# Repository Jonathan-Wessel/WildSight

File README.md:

# WildSights Rhino Detection Camera Node

This project is an ESP32-S3 wildlife monitoring camera node that detects rhinos using an Edge Impulse object detection model. The device is triggered by a PIR motion sensor, captures a grayscale image, runs inference on-device, saves the captured image to an SD card, and sends a LoRaWAN uplink message with the detection result.

The project is currently configured for the `ESP32S3-EYE` camera model.

---

## Features

- PIR motion-triggered image capture
- ESP32-S3 camera support
- Edge Impulse object detection
- Rhino detection using bounding box results
- Grayscale QVGA camera capture
- SD card image saving as JPEG
- LoRaWAN uplinks using LMIC
- IR LED control for low-light image capture
- FreeRTOS task for image capture and inference

---

## Important Board Manager Version

Use the following ESP32 board package version:

```text
ESP32 by Espressif Systems version 2.0.17
```

In the Arduino IDE:

1. Open **Tools > Board > Boards Manager**
2. Search for **esp32**
3. Install **esp32 by Espressif Systems**
4. Select version **2.0.17**

Using a newer or different ESP32 board package version may cause compatibility issues with the camera, PSRAM, SD card, or libraries.

---

## Hardware Requirements

- ESP32-S3 camera board
- ESP32S3-EYE compatible camera pin configuration
- PIR motion sensor
- IR LED or IR illuminator
- Light sensor
- SD card
- LoRa radio module
- LoRaWAN gateway
- LoRaWAN network server, such as The Things Network

---

## Software Requirements

- Arduino IDE
- ESP32 Arduino board package version `2.0.17`
- MCCI LoRaWAN LMIC library
- Edge Impulse Arduino library exported from the Edge Impulse project
- ESP32 camera support
- SD_MMC support

The sketch also requires these project files:

```cpp
#include "camera_pins.h"
#include "sd_read_write.h"
```

Make sure these files are included in the sketch folder or are available through the correct library or example source.

---

## Recommended Arduino IDE Settings

| Setting | Value |
|---|---|
| Board package | ESP32 by Espressif Systems `2.0.17` |
| Board | ESP32S3 Dev Module or compatible ESP32-S3 camera board |
| PSRAM | Enabled |
| Upload speed | 921600 or lower if upload fails |
| Serial monitor baud | 115200 |
| Partition scheme | Huge APP or another large-app partition |

The exact board option may depend on the ESP32-S3 camera board being used.

---

## Pin Configuration

### Sensor and Output Pins

| Function | GPIO |
|---|---:|
| PIR sensor | GPIO 1 |
| IR LED | GPIO 2 |
| Light sensor | GPIO 46 |

### LoRa Radio Pins

| Function | GPIO |
|---|---:|
| NSS / CS | GPIO 3 |
| RESET | GPIO 14 |
| DIO0 | GPIO 20 |
| DIO1 | GPIO 21 |
| MISO | GPIO 47 |
| MOSI | GPIO 19 |
| SCK | GPIO 45 |

These pins are defined in the sketch:

```cpp
#define GPIO_PIR         1
#define GPIO_IRLED       2
#define GPIO_LIGHTSENSOR 46

#define PIN_NSS   3
#define PIN_RST   14
#define PIN_DIO0  20
#define PIN_DIO1  21

#define LORA_MISO  47
#define LORA_MOSI  19
#define LORA_SCK   45
```

Check that the pin definitions match the actual wiring of your ESP32-S3 board and LoRa module.

---

## Camera Configuration

The project is configured for:

```cpp
#define CAMERA_MODEL_ESP32S3_EYE
```

The camera captures grayscale QVGA images:

```cpp
.pixel_format = PIXFORMAT_GRAYSCALE,
.frame_size   = FRAMESIZE_QVGA,
```

This means the camera captures images at:

```text
320 x 240
```

The frame buffer is stored in PSRAM:

```cpp
.fb_location = CAMERA_FB_IN_PSRAM
```

Because of this, PSRAM must be enabled in the Arduino IDE board settings.

---

## Edge Impulse Model

The project uses an exported Edge Impulse model:

```cpp
#include <Wildsights_rhino_md_conf.5_inferencing.h>
```

The classifier is initialized in `setup()`:

```cpp
run_classifier_init();
```

Inference is run using:

```cpp
EI_IMPULSE_ERROR err = run_classifier(&signal, &result, false);
```

The code checks the Edge Impulse bounding box results for the label:

```text
rhino
```

The label comparison happens here:

```cpp
if (strcmp(bb.label, "rhino") == 0)
```

If your Edge Impulse model uses a different label name, update this line in the sketch.

---

## Detection Threshold

The rhino detection confidence threshold is currently set to `0.7`:

```cpp
if (rhino && best.value >= 0.7) {
```

Threshold behavior:

| Threshold | Behavior |
|---|---|
| `0.5` | More sensitive, but may create more false positives |
| `0.7` | Current default |
| `0.9` | More strict, but may miss some detections |

---

## LoRaWAN Configuration

The sketch uses OTAA activation with:

- Join EUI
- Device EUI
- App Key

These values are defined in the code:

```cpp
static const uint8_t JOIN_EUI_BE[8] = { ... };
static const uint8_t DEV_EUI_BE[8]  = { ... };
static const uint8_t APP_KEY[16]    = { ... };
```

Do not publish real LoRaWAN credentials in a public repository.

For public repositories, replace real credentials with placeholder values:

```cpp
static const uint8_t JOIN_EUI_BE[8] = {
  0x00, 0x00, 0x00, 0x00,
  0x00, 0x00, 0x00, 0x00
};

static const uint8_t DEV_EUI_BE[8] = {
  0x00, 0x00, 0x00, 0x00,
  0x00, 0x00, 0x00, 0x00
};

static const uint8_t APP_KEY[16] = {
  0x00, 0x00, 0x00, 0x00,
  0x00, 0x00, 0x00, 0x00,
  0x00, 0x00, 0x00, 0x00,
  0x00, 0x00, 0x00, 0x00
};
```

If real keys were shared publicly, regenerate them in your LoRaWAN network server.

---

## LMIC Configuration

The LoRa radio uses custom SPI pins:

```cpp
SPI.begin(LORA_SCK, LORA_MISO, LORA_MOSI, PIN_NSS);
```

LMIC is initialized in `setup()`:

```cpp
os_init();
LMIC_reset();
LMIC_selectSubBand(1);
LMIC_setAdrMode(0);
LMIC_setClockError(MAX_CLOCK_ERROR * 1 / 100);
LMIC_startJoining();
```

The selected LoRaWAN sub-band is:

```cpp
LMIC_selectSubBand(1);
```

Make sure this matches your LoRaWAN region, gateway, and network server configuration.

---

## LoRaWAN Uplink Messages

When a rhino is detected, the node sends:

```text
Rhino detected
```

When no rhino is detected, the node sends:

```text
No Rhino
```

Messages are sent on LoRaWAN port `1`:

```cpp
LMIC_setTxData2(1, buf, (u1_t)len, 0);
```

---

## SD Card Image Saving

Images are saved to:

```text
/camera/
```

The directory is created during setup:

```cpp
createDir(SD_MMC, "/camera");
```

Images are saved using an incrementing file number:

```text
/camera/1.jpg
/camera/2.jpg
/camera/3.jpg
```

Both rhino detections and non-detections are currently saved.

---

## How It Works

1. The ESP32-S3 starts the serial monitor, SD card, camera, Edge Impulse model, LoRa radio, and PIR interrupt.
2. The PIR sensor triggers an interrupt when motion is detected.
3. A FreeRTOS inference task wakes up.
4. The PIR signal is debounced.
5. The IR LED turns on.
6. The camera captures a grayscale image.
7. The image is resized to the Edge Impulse model input size.
8. The Edge Impulse classifier runs on the ESP32-S3.
9. The result is checked for a bounding box labeled `rhino`.
10. If the confidence is at least `0.7`, a rhino detection is confirmed.
11. The image is saved to the SD card.
12. A LoRaWAN message is queued.
13. The IR LED turns off.
14. The system waits through a cooldown period before responding to another trigger.

---

## Main Runtime Loop

The main `loop()` only runs the LMIC event loop:

```cpp
void loop() {
  os_runloop_once();
}
```

Image capture and inference are handled in a separate FreeRTOS task:

```cpp
xTaskCreatePinnedToCore(
  inferenceTask,
  "inferenceTask",
  32768,
  nullptr,
  1,
  &inferTaskHandle,
  1
);
```

---

## Serial Monitor

Open the Serial Monitor at:

```text
115200 baud
```

Startup messages include:

```text
PSRAM found: YES
Free heap:
Free PSRAM:
Camera PID:
Setup complete.
```

LoRaWAN messages include:

```text
Joining...
JOINED!
Uplink queued: Rhino detected
TX complete
```

Inference messages include:

```text
INFERENCE: running classifier
INFERENCE: done classifier
Rhino DETECTED
No rhino.
```

---

## Troubleshooting

### Camera Init Failed

Check the following:

- The correct camera model is selected
- `camera_pins.h` matches your board
- PSRAM is enabled
- ESP32 board package version is `2.0.17`
- The camera ribbon cable is connected correctly

### Failed to Allocate Snapshot Buffer

Check the following:

- PSRAM is enabled
- The board has PSRAM
- The Edge Impulse model is not too large
- The partition scheme provides enough app space

### Device Does Not Join LoRaWAN

Check the following:

- Join EUI
- Device EUI
- App Key
- EUI byte order
- LMIC region
- LMIC sub-band
- Gateway frequency plan
- LoRa radio wiring
- Antenna connection

### SD Card Images Are Not Saving

Check the following:

- SD card is inserted
- SD card is formatted correctly
- `sdmmcInit()` succeeds
- The `/camera` directory exists
- `sd_read_write.h` is included correctly

### Classifier Always Returns No Rhino

Check the following:

- The model label is exactly `rhino`
- The detection threshold is not too high
- The camera image orientation is correct
- The IR LED provides enough illumination
- The training data matches the deployment environment
- The model was exported correctly from Edge Impulse

---

## Notes

The function:

```cpp
saveGrayJpegWithBox()
```

saves the grayscale camera frame as a JPEG image.

In the current version of the sketch, the bounding box is printed to the Serial Monitor but is not drawn onto the saved image.

The bounding box output is printed here:

```cpp
Serial.printf(
  "Rhino DETECTED label = %s : conf=%.3f box(x=%u y=%u w=%u h=%u)\n",
  best.label,
  best.value,
  best.x,
  best.y,
  best.width,
  best.height
);
```

---

## Deployment Notes

- Use a weatherproof enclosure for outdoor deployment.
- Protect the camera lens, PIR sensor, and electronics from rain.
- Use a stable power supply.
- Connect the LoRa antenna before transmitting.
- Test the camera, SD card, Edge Impulse model, and LoRaWAN join process before field deployment.
- Do not publish real LoRaWAN credentials.

---

## License

Add the project license here.

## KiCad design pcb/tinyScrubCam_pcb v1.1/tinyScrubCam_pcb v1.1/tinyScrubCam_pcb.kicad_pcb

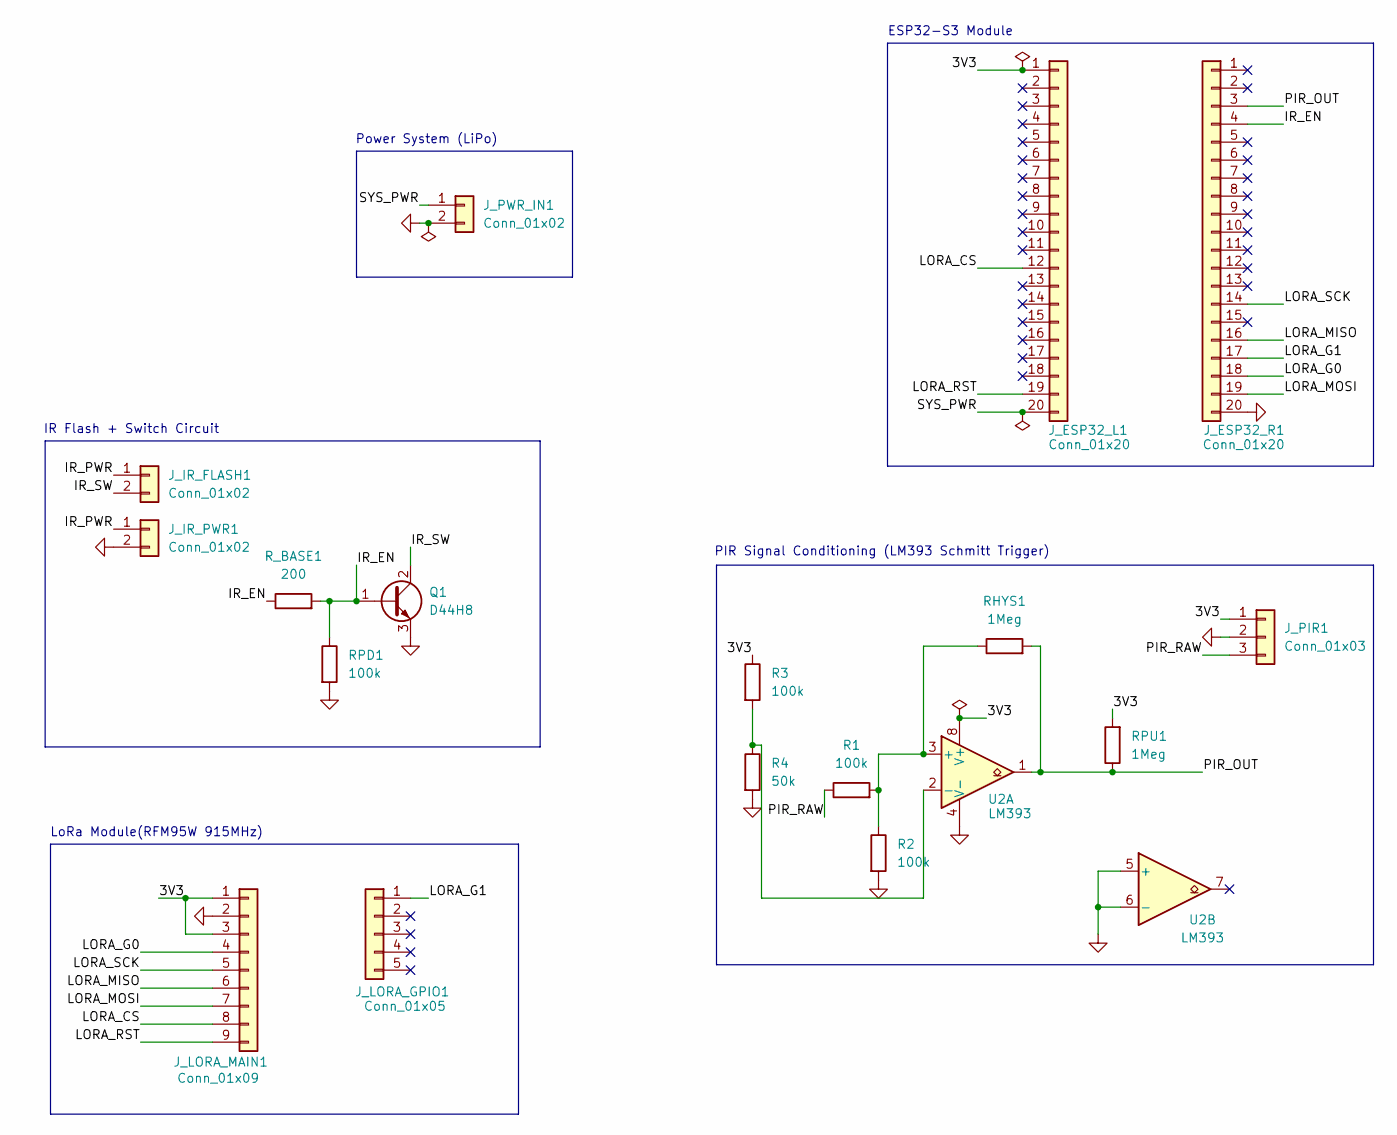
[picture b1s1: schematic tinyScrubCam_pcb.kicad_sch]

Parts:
J_ESP32_L1, J_ESP32_R1: Conn_01x20; PinHeader_1x20_P2.54mm_Vertical
J_IR_FLASH1: Conn_01x02; PinHeader_1x02_P2.54mm_Vertical
J_IR_PWR1: Conn_01x02; PinHeader_1x02_P2.54mm_Vertical
J_LORA_GPIO1: Conn_01x05; PinHeader_1x05_P2.54mm_Vertical
J_LORA_MAIN1: Conn_01x09; PinHeader_1x09_P2.54mm_Vertical
J_PIR1: Conn_01x03; PinSocket_1x03_P2.54mm_Vertical
J_PWR_IN1: Conn_01x02; JST_PH_B2B-PH-K_1x02_P2.00mm_Vertical
Q1: D44H8; TO-220-3_Vertical
R1, R2, R3: 100k; R_Axial_DIN0207_L6.3mm_D2.5mm_P10.16mm_Horizontal
R4: 50k; R_Axial_DIN0207_L6.3mm_D2.5mm_P10.16mm_Horizontal
RHYS1: 1Meg; R_Axial_DIN0207_L6.3mm_D2.5mm_P10.16mm_Horizontal
RPD1: 100k; R_Axial_DIN0207_L6.3mm_D2.5mm_P10.16mm_Horizontal
RPU1: 1Meg; R_Axial_DIN0207_L6.3mm_D2.5mm_P10.16mm_Horizontal
R_BASE1: 200; R_Axial_DIN0207_L6.3mm_D2.5mm_P10.16mm_Horizontal
U2: LM393

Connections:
/3V3: J_ESP32_L1.1 (3V3), J_LORA_MAIN1.1 (3V3), J_LORA_MAIN1.3 (EN), J_PIR1.1, R3.1, RPU1.2, U2.8 (V+); also elsewhere on the board
/IR_EN: J_ESP32_R1.4 (GPIO2), Q1.1 (B), RPD1.1, R_BASE1.1, R_BASE1.2
/IR_PWR: J_IR_FLASH1.1, J_IR_PWR1.1
/IR_SW: J_IR_FLASH1.2, Q1.2 (C)
/LORA_CS: J_ESP32_L1.12 (GPIO3), J_LORA_MAIN1.8 (CS)
/LORA_G0: J_ESP32_R1.18 (GPIO20), J_LORA_MAIN1.4 (GPIO0)
/LORA_G1: J_ESP32_R1.17 (GPIO21), J_LORA_GPIO1.1 (GPIO1_1)
/LORA_MISO: J_ESP32_R1.16 (GPIO47), J_LORA_MAIN1.6 (MISO)
/LORA_MOSI: J_ESP32_R1.19 (GPIO19), J_LORA_MAIN1.7 (MOSI)
/LORA_RST: J_ESP32_L1.19 (GPIO14), J_LORA_MAIN1.9 (RST)
/LORA_SCK: J_ESP32_R1.14 (GPIO45), J_LORA_MAIN1.5 (SCK)
/PIR_OUT: J_ESP32_R1.3 (GPIO1), RHYS1.2, RPU1.1, U2.1
/PIR_RAW: J_PIR1.3, R1.1; also elsewhere on the board
/SYS_PWR: J_ESP32_L1.20 (5V), J_PWR_IN1.1
GND: J_ESP32_R1.20 (GND), J_IR_PWR1.2, J_LORA_MAIN1.2 (GND), J_PIR1.2, J_PWR_IN1.2, Q1.3 (E), R2.2, R4.2, RPD1.2, U2.4 (V-), U2.5 (+), U2.6 (-); also elsewhere on the board
unnamed: R1.2, R2.1, RHYS1.1, U2.3 (+)
unnamed: R3.2, R4.1, U2.2 (-)

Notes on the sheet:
ESP32-S3 Module
IR Flash + Switch Circuit
Power System (LiPo)
LoRa Module(RFM95W 915MHz)
PIR Signal Conditioning (LM393 Schmitt Trigger)

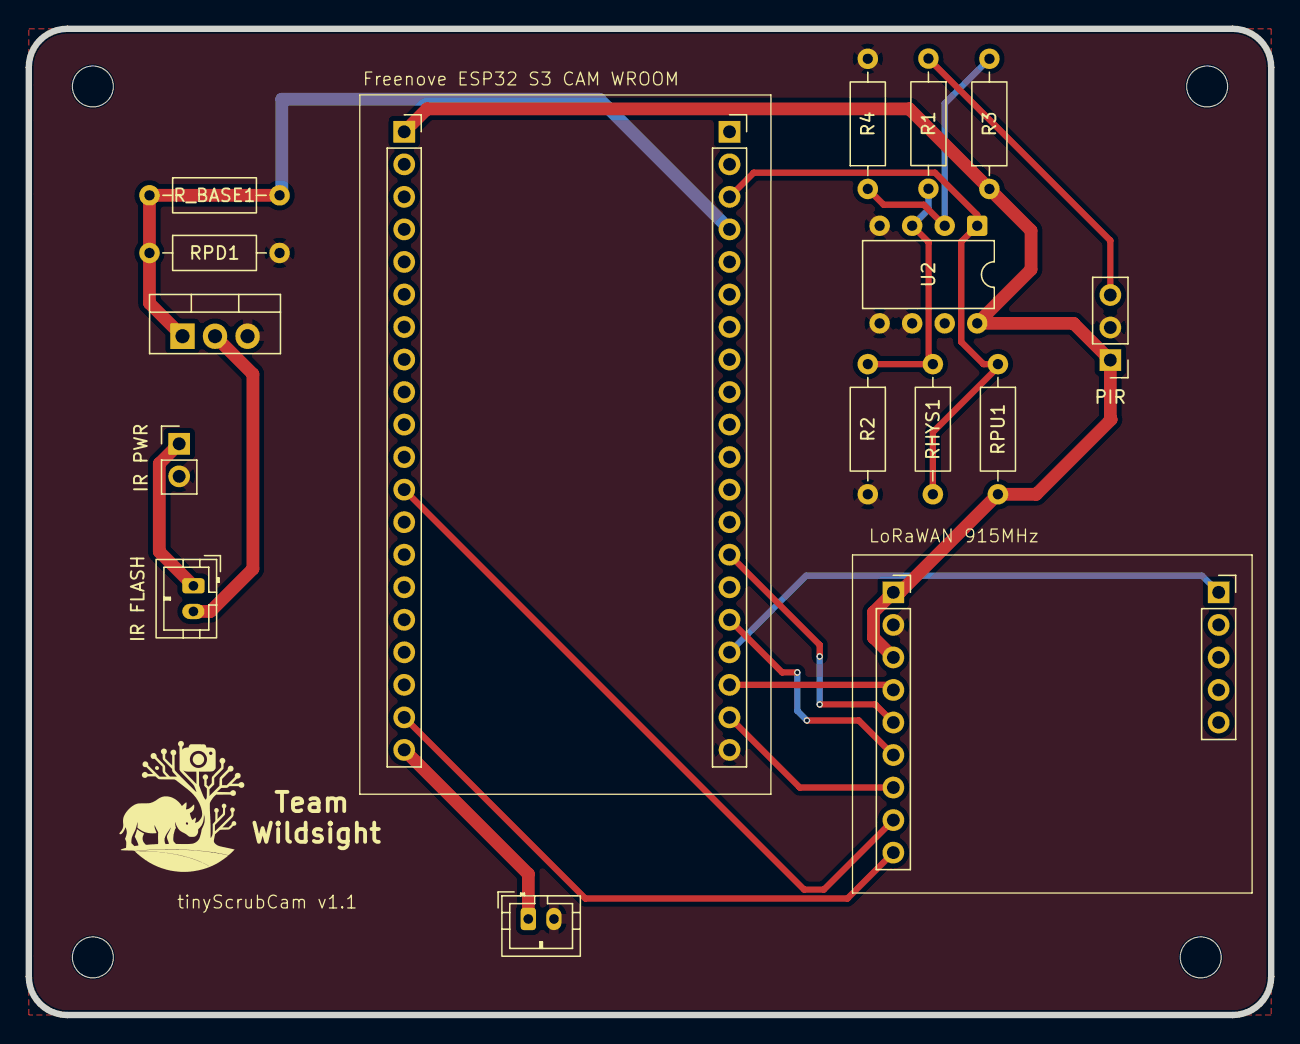
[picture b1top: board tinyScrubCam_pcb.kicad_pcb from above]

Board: 2 copper layers, 97.0 x 77.0 mm, 18 parts (0 on the bottom side), 17 nets.

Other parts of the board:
PIR: Conn_01x03; PinHeader_1x03_P2.54mm_Vertical

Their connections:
/3V3: PIR.1; also elsewhere on the board
/PIR_RAW: PIR.3; also elsewhere on the board
GND: PIR.2; also elsewhere on the board

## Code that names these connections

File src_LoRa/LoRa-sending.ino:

#include <Arduino.h>
#include <lmic.h>
#include <hal/hal.h>
#include <SPI.h>
#include <string.h>

static const uint8_t JOIN_EUI_BE[8] = { 0x00,0x00,0x00,0x00,0x00,0x00,0x00,0x00 };
static const uint8_t DEV_EUI_BE[8]  = { 0x70,0xB3,0xD5,0x7E,0xD8,0x00,0x50,0x7F };
static const uint8_t APP_KEY[16]    = {
  0x6E,0x2C,0xB9,0x5B,0x06,0x57,0x13,0x4B,
  0x9B,0xCC,0xEC,0x15,0xB6,0x5C,0x51,0x74
};

void os_getArtEui (u1_t* buf) { for (int i=0;i<8;i++) buf[i] = JOIN_EUI_BE[7-i]; }
void os_getDevEui (u1_t* buf) { for (int i=0;i<8;i++) buf[i] = DEV_EUI_BE[7-i]; }
void os_getDevKey (u1_t* buf) { memcpy(buf, APP_KEY, 16); }

// LoRa pins
static const uint8_t PIN_NSS  = 3;    // CS/NSS
static const uint8_t PIN_RST  = 14;   // RESET
static const uint8_t PIN_DIO0 = 20;   // DIO0
static const uint8_t PIN_DIO1 = 21;   // DIO1

// Custom SPI pins
static const uint8_t LORA_MISO = 47;
static const uint8_t LORA_MOSI = 48;
static const uint8_t LORA_SCK  = 45;

const lmic_pinmap lmic_pins = {
  .nss = PIN_NSS,
  .rxtx = LMIC_UNUSED_PIN,
  .rst = PIN_RST,
  .dio = { PIN_DIO0, PIN_DIO1, LMIC_UNUSED_PIN }
};

static osjob_t sendjob;

// ---- Payload queue ----
static char pendingMsg[51];   // keep <= 51 for safety at lower DRs
static volatile bool havePendingMsg = false;

// Forward decl
void do_send(osjob_t*);

// Queue any string payload (ASCII)
bool sendString(const char* s) {
  if (s == nullptr) return false;

  size_t len = strnlen(s, sizeof(pendingMsg)-1);
  if (len == 0) return false;

  // Store it for sending
  memset(pendingMsg, 0, sizeof(pendingMsg));
  memcpy(pendingMsg, s, len);
  havePendingMsg = true;

  // Try immediate send (or it will retry from do_send)
  do_send(&sendjob);
  return true;
}

// Call this from your camera/model code when rhino is confirmed
void queueSendRhinoDetected() {
  sendString("Rhino detected");
}

void do_send(osjob_t*) {
  // Must be joined (LMIC.devaddr becomes non-zero after join)
  if (LMIC.devaddr == 0) {
    // not joined yet; keep message pending
    return;
  }

  // Radio busy?
  if (LMIC.opmode & OP_TXRXPEND) {
    // retry soon
    os_setTimedCallback(&sendjob, os_getTime() + ms2osticks(500), do_send);
    return;
  }

  if (!havePendingMsg) return;

  // Convert message to bytes (no null terminator)
  uint8_t buf[51];
  size_t len = strnlen(pendingMsg, sizeof(pendingMsg));
  memcpy(buf, pendingMsg, len);

  LMIC_setTxData2(/*port*/1, buf, (u1_t)len, /*confirmed*/0);

  Serial.print("Uplink queued: ");
  Serial.println(pendingMsg);

  havePendingMsg = false;
}

void onEvent(ev_t ev) {
  Serial.print("[LMIC] ");
  Serial.println((unsigned)ev);

  if (ev == EV_JOINING) Serial.println("Joining...");

  if (ev == EV_JOINED) {
    Serial.println("JOINED!");
    LMIC_setLinkCheckMode(0);

    // If something was queued before join completed, send it now
    do_send(&sendjob);
  }

  if (ev == EV_JOIN_FAILED || ev == EV_JOIN_TXCOMPLETE) {
    Serial.println("Join not accepted (keys/subband/pins/frequency-plan issue)");
  }

  if (ev == EV_TXCOMPLETE) {
    Serial.println("TX complete");

    // Optional: schedule periodic retry send if you want periodic telemetry.
    // For your case (event-based), you can remove this entirely.
    // os_setTimedCallback(&sendjob, os_getTime() + sec2osticks(30), do_send);
  }
}

void setup() {
  Serial.begin(115200);
  delay(1500);

  SPI.begin(LORA_SCK, LORA_MISO, LORA_MOSI, PIN_NSS);

  os_init();
  LMIC_reset();

  // US915 subband (adjust to match your gateway FSB)
  LMIC_selectSubBand(1);

  LMIC_setAdrMode(0);
  LMIC_setClockError(MAX_CLOCK_ERROR * 1 / 100);

  LMIC_startJoining();

  // --- TEST: comment this out once you hook camera trigger ---
  // queueSendRhinoDetected();
}

void loop() {
  os_runloop_once();

  // Example hook point:
  // if (rhinoConfirmedThisFrame) queueSendRhinoDetected();
}

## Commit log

2025-11-01 Create LoRa
2026-02-02 Delete src/SeniorDesignBaseSketch.ino
    Replacing this file
2026-02-03 Added the LoRa, and fixed ReadMe and Folders
2026-02-10 Deleting Old files From MAX78000
2026-02-10 Added a new ReadMe
2026-02-10 fix Readme
2026-02-13 Added EdgeImpulse Inferencing Code without microSD card implementation and changed the zip file to be added to library
2026-02-13 This is the code to send a rhino detection integrated with the photo
2026-02-19 Current EdgeImpulseModel code and saves images to microSD
2026-03-06 Adding the integrated code
2026-04-01 Changed Zip file to be added to lirbary to contain two classes
2026-04-01 Reorganized Integrated folder to contain all necessary files for it to run
2026-04-01 Set Camera config values, switch from QVGA to VGA to increase framesize to 640x480 instead of 320x240
2026-04-01 Finished cameraInitGray() function, contains 3 camera settings that can be altered for better inferecning results
2026-04-01 Finished ei_camera_get_data() function
2026-04-01 Finished captureForEI function
2026-04-01 Commented out all PIR/LORA stuff so I am able to test inferencing
2026-04-02 Inference is working, not working well, commented out both the LORA and PIR functions to for testing
2026-04-14 Current Integrated EdgeImpulseModel, PIR, IR, and LORA are commented out
2026-05-01 Fully Integrated Code, Contains 3 libraries, Original Rhino Model, 2 Class Rhino Model and Dog Model, Deleted all other irrelevant files
2026-05-08 Added most recent code and Read.me
